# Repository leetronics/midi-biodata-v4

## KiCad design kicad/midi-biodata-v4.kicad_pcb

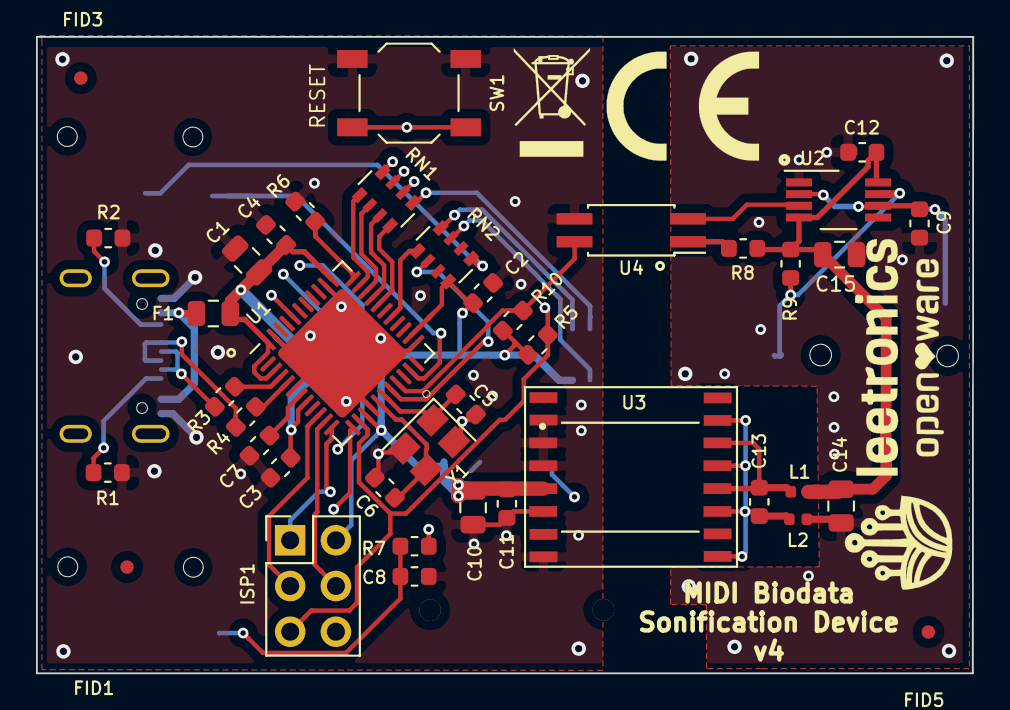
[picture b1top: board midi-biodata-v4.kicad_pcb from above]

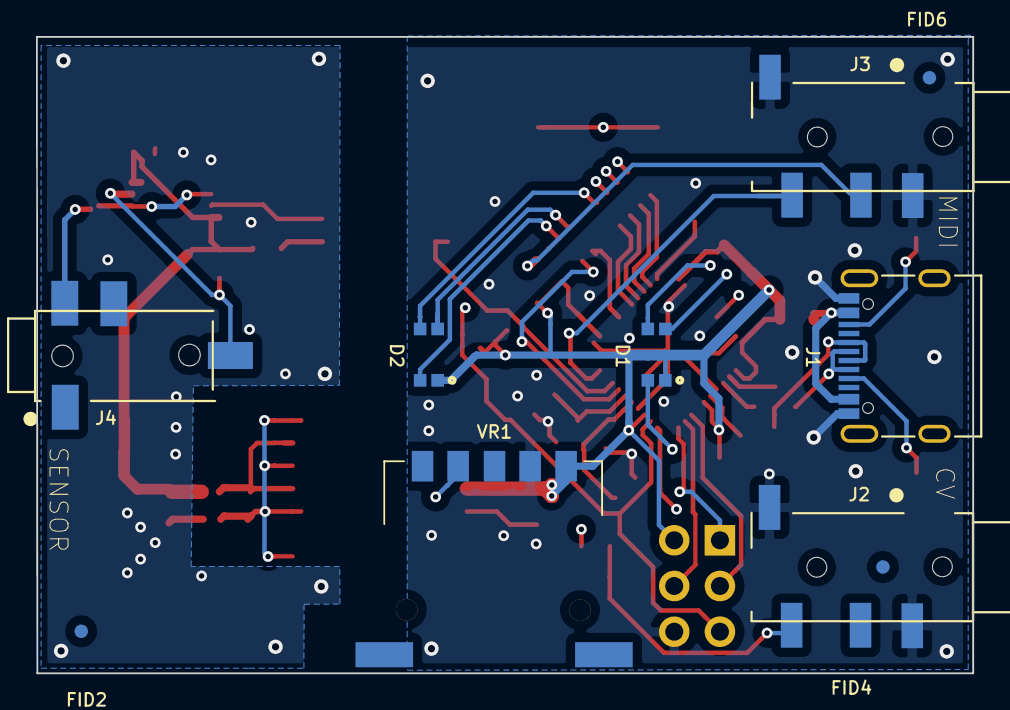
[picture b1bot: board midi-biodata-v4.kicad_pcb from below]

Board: 4 copper layers, 52.0 x 35.4 mm, 51 parts (10 on the bottom side), 43 nets.

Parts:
C1, C14, C15: 4.7uF; C_0805_2012Metric
C2, C3, C4, C11, C12, C13: 0.1uF; C_0603_1608Metric
C5, C6: 22pF; C_0603_1608Metric
C7, C8: 1uF; C_0603_1608Metric
C9: 4200pF; C_0603_1608Metric
C10: 4,7uF; C_0805_2012Metric
D1, D2: LED_RGBA; LED_RGB_EASR3212RGBA0
F1: Fuse; Fuse_0805_2012Metric
FID1, FID2, FID3, FID4, FID5, FID6: Fiducial; Fiducial_0.75mm_Mask1.5mm
ISP1: AVR-ISP-6; PinHeader_2x03_P2.54mm_Vertical
J1: USB_C_Receptacle_USB2.0; USB_C_Receptacle_Palconn_UTC16-G
J2: CV; PJ-320-4A
J3: MIDI; PJ-320-4A
J4: SENSOR; PJ-226-4A
L1, L2: L; R_0402_1005Metric
R1, R2, R7: 5,1K; R_0603_1608Metric
R3, R4: 27R; R_0603_1608Metric
R5, R10: 10K; R_0603_1608Metric
R6: 0R; R_0603_1608Metric
R8: 1K; R_0603_1608Metric
R9: 100K; R_0603_1608Metric
RN1, RN2: R_Pack04; R_Array_Convex_4x0603
Ref**: Val**; drawing
SW1: SW_Push; SW_SPST_TL3342
U1: ATmega32U4-MU; QFN-44-1EP_7x7mm_P0.5mm_EP5.2x5.2mm
U2: LM555; VSSOP-8_3.0x3.0mm_P0.65mm
U3: ADUM5028-5BRIZ-ADUM5028-5BRIZ-midi-biodata-esp32_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; SOIC127P1031X265-8N
U4: LTV-355T; SO-4_4.4x2.3mm_P1.27mm
VR1: RK14J12R0A0C
Y1: Crystal; Crystal_SMD_3225-4Pin_3.2x2.5mm

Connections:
555: U2.3, U4.2
+5V: C1.1, C2.1, C3.1, C4.1, C10.2, C11.2, D1.1, D2.1, F1.1, ISP1.2, R5.2, R10.1, RN2.4, U1.2, U1.7, U1.14, U1.24, U1.34, U1.44, U3.3, VR1.1
+5VA: C12.1, C14.1, C15.1, L1.1, R8.1, R9.1, U2.4, U2.8
GND: C1.2, C2.2, C3.2, C4.2, C5.1, C6.2, C7.2, C8.2, C10.1, C11.1, ISP1.6, J1.A1, J1.A12, J1.B1, J1.B12, J2.1, J2.4, J3.1, J3.4, R1.1, R2.1, R6.1, SW1.1, U1.5, U1.15, U1.23, U1.35, U1.43, U1.45, U3.1, U3.2, U3.4, U4.3, VR1.2, Y1.2, Y1.4
GNDA: C9.2, C12.2, C14.2, C15.2, L2.2, U2.1
ISO_OUT: R10.2, U1.19, U4.4
MISO: ISP1.1, U1.11
MOSI: ISP1.4, U1.10
unnamed: C5.2, U1.17, Y1.1
unnamed: C6.1, U1.16, Y1.3
unnamed: C7.1, U1.6
unnamed: C8.1, J2.2, R7.1
unnamed: C9.1, J4.1, U2.2, U2.6
unnamed: C13.1, L1.2, U3.6, U3.8
unnamed: C13.2, L2.1, U3.5, U3.7
unnamed: D1.2, RN1.6
unnamed: D1.3, RN1.7
unnamed: D1.4, RN1.8
unnamed: D2.2, RN2.8
unnamed: D2.3, RN1.5
unnamed: D2.4, RN2.7
unnamed: F1.2, J1.A4, J1.A9, J1.B4, J1.B9
unnamed: J1.A5, R1.2
unnamed: J1.A6, J1.B6, R4.2
unnamed: J1.A7, J1.B7, R3.2
unnamed: J1.B5, R2.2
unnamed: J3.3, RN2.5
unnamed: J4.2, R9.2, U2.7
unnamed: R3.1, U1.3
unnamed: R4.1, U1.4
unnamed: R6.2, U1.33
unnamed: R7.2, U1.12
unnamed: R8.2, U4.1
unnamed: U1.40, VR1.4
PB5: RN1.4, U1.29
PB6: RN1.3, U1.30
PC6: RN1.2, U1.31
PC7: RN1.1, U1.32
PD0: RN2.2, U1.18
PD7: RN2.1, U1.27
RESET: ISP1.5, R5.1, SW1.2, U1.13
SCK: ISP1.3, U1.9
TX0: J3.2, U1.21

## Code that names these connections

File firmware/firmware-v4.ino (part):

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const word TCNT1_TOP = 16000000 / (2 * PWM_FREQ_HZ);


#define LED_D1_R_PIN 13 // PC7 - D1 R
#define LED_D1_G_PIN 5  // PC6 - D1 G
#define LED_D1_B_PIN 10 // PB6 - D1 B
#define LED_D2_R_PIN 9  // PB5 - D2 R 
#define LED_D2_G_PIN 3 // PD0  - D2 G
#define LED_D2_B_PIN 6 // PD7 - D2 B

#define LED_NUM 7
LEDFader leds[LED_NUM] = { // 6 LEDs (perhaps 2 RGB LEDs)
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
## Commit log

2024-09-27 initial project upload
